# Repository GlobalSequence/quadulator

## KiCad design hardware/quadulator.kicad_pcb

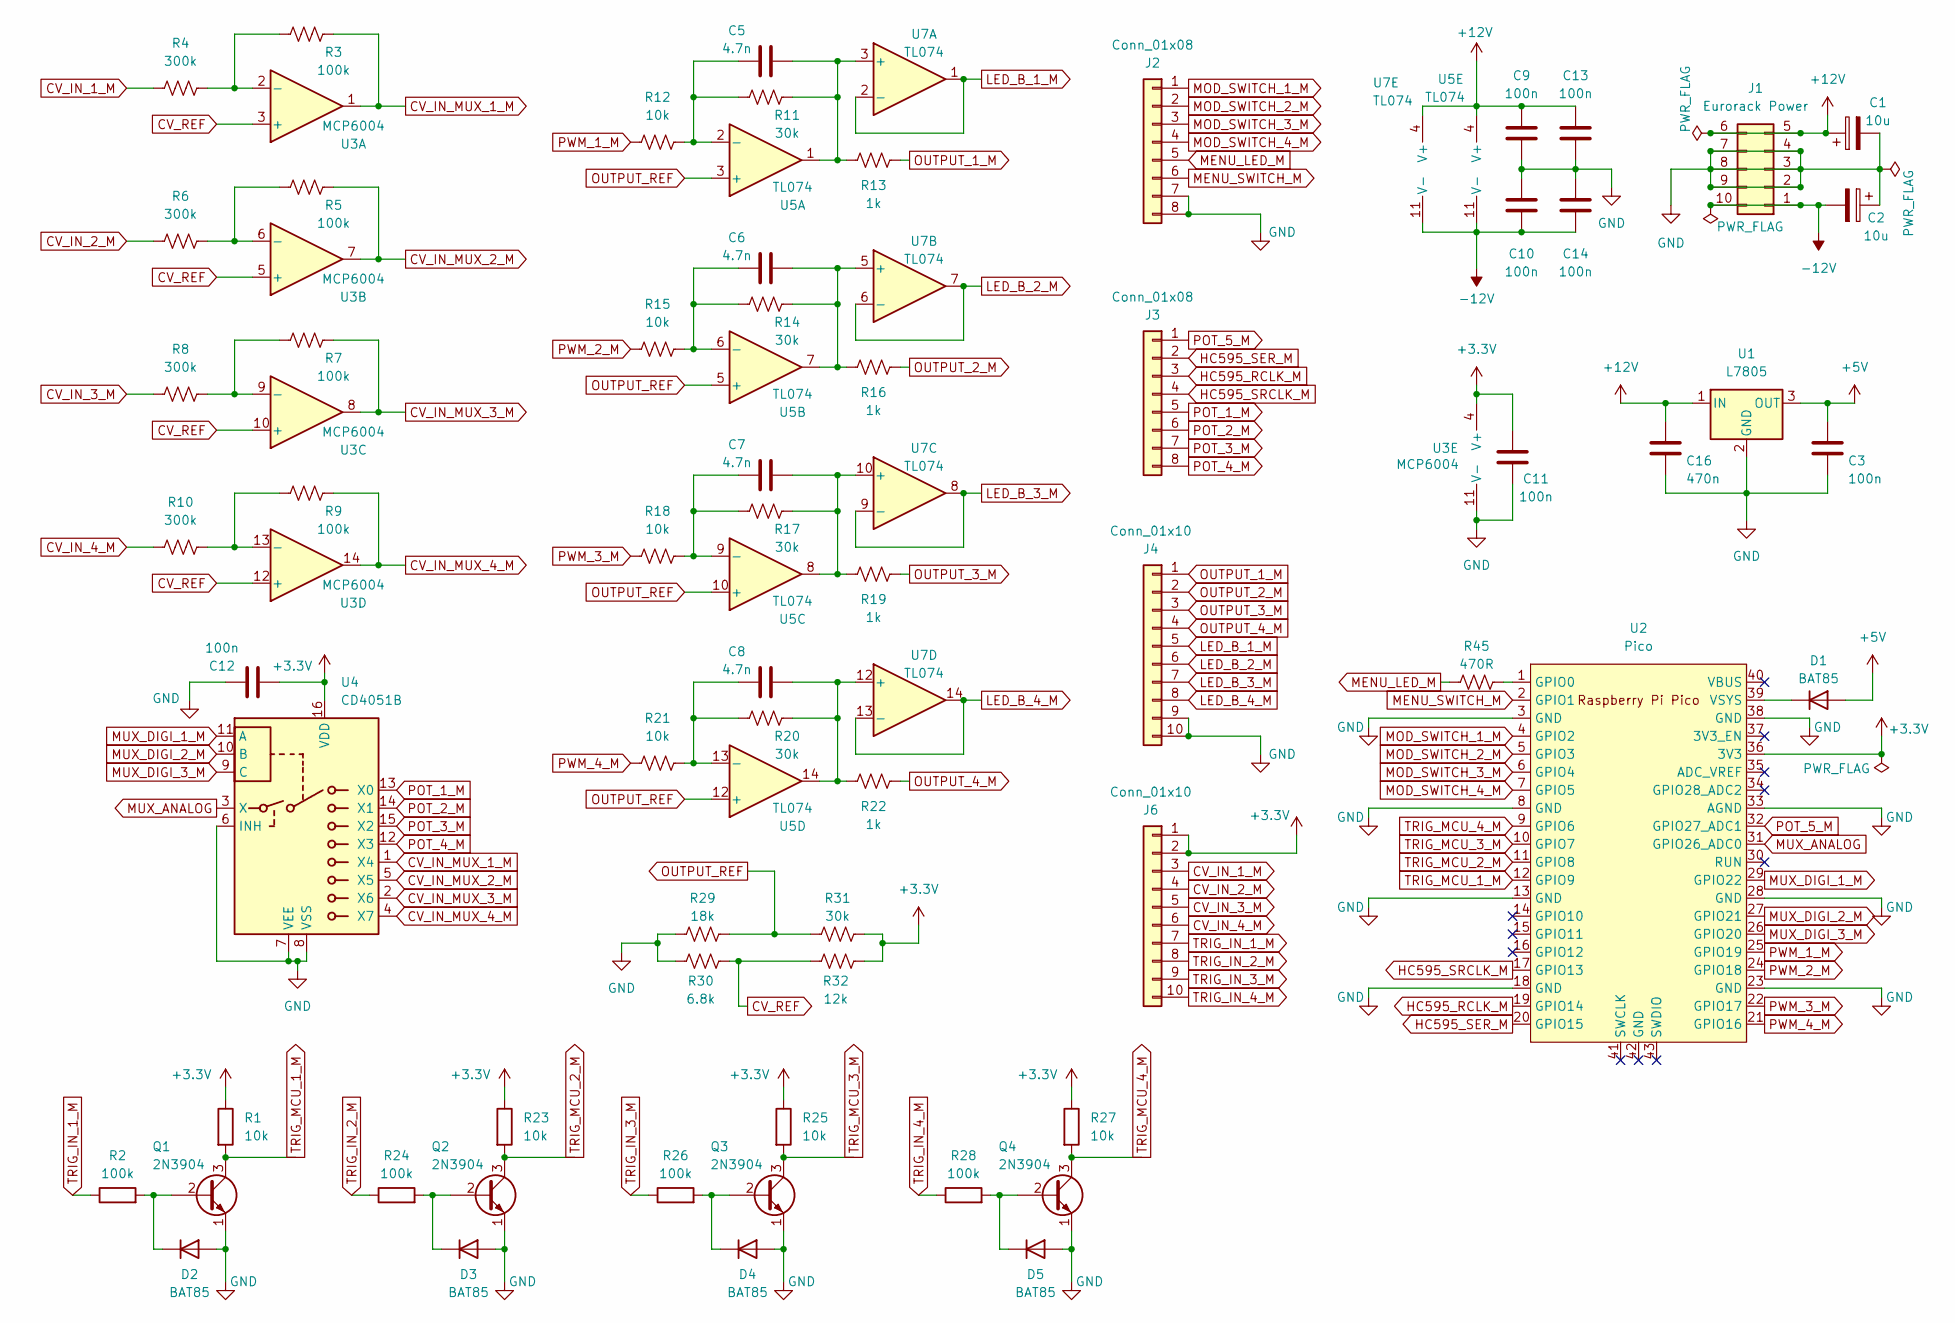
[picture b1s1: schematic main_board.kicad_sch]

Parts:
C1, C2: 10u; CP_Radial_D5.0mm_P2.50mm
C3, C9, C10, C11, C12, C13, C14: 100n; C_Disc_D5.0mm_W2.5mm_P5.00mm
C5, C6, C7, C8: 4.7n; C_Disc_D5.0mm_W2.5mm_P5.00mm
C16: 470n; C_Disc_D5.0mm_W2.5mm_P5.00mm
D1, D2, D3, D4, D5: BAT85; D_A-405_P7.62mm_Horizontal
J1: Eurorack Power; IDC-Header_2x05_P2.54mm_Vertical
J2, J3: Conn_01x08; PinSocket_1x08_P2.54mm_Vertical
J4, J6: Conn_01x10; PinSocket_1x10_P2.54mm_Vertical
Q1, Q2, Q3, Q4: 2N3904; TO-92L_Inline_Wide
R1, R12, R15, R18, R21, R23, R25, R27: 10k; R_Axial_DIN0207_L6.3mm_D2.5mm_P7.62mm_Horizontal
R2, R3, R5, R7, R9, R24, R26, R28: 100k; R_Axial_DIN0207_L6.3mm_D2.5mm_P7.62mm_Horizontal
R4, R6, R8, R10: 300k; R_Axial_DIN0207_L6.3mm_D2.5mm_P7.62mm_Horizontal
R11, R14, R17, R20, R31: 30k; R_Axial_DIN0207_L6.3mm_D2.5mm_P7.62mm_Horizontal
R13, R16, R19, R22: 1k; R_Axial_DIN0207_L6.3mm_D2.5mm_P7.62mm_Horizontal
R29: 18k; R_Axial_DIN0207_L6.3mm_D2.5mm_P7.62mm_Horizontal
R30: 6.8k; R_Axial_DIN0207_L6.3mm_D2.5mm_P7.62mm_Horizontal
R32: 12k; R_Axial_DIN0207_L6.3mm_D2.5mm_P7.62mm_Horizontal
R45: 470R; R_Axial_DIN0207_L6.3mm_D2.5mm_P7.62mm_Horizontal
U1: L7805; TO-220-3_Vertical
U2: Pico; RPi_Pico_SMD_TH
U3: MCP6004; DIP-14_W7.62mm_Socket
U4: CD4051B; DIP-16_W7.62mm_Socket
U5, U7: TL074; DIP-14_W7.62mm_Socket

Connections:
+3.3V: C11.1, C12.2, J6.1, J6.2, R1.1, R23.1, R25.1, R27.1, R31.2, R32.1, U2.36 (3V3), U3.4 (V+), U4.16 (VDD); also elsewhere on the board
+5V: C3.1, D1.2 (A), U1.3 (OUT)
+12V: C1.1, C9.1, C13.1, C16.1, J1.5, J1.6, U1.1 (IN), U5.4 (V+), U7.4 (V+)
-12V: C2.2, C10.2, C14.2, J1.1, J1.10, U5.11 (V-), U7.11 (V-)
CV_IN_1_M: J6.3, R4.1
CV_IN_2_M: J6.4, R6.1
CV_IN_3_M: J6.5, R8.1
CV_IN_4_M: J6.6, R10.1
CV_IN_MUX_1_M: R3.2, U3.1, U4.1 (X4)
CV_IN_MUX_2_M: R5.2, U3.7, U4.5 (X5)
CV_IN_MUX_3_M: R7.2, U3.8, U4.2 (X6)
CV_IN_MUX_4_M: R9.2, U3.14, U4.4 (X7)
CV_REF: R30.1, R32.2, U3.3 (+), U3.5 (+), U3.10 (+), U3.12 (+)
GND: C1.2, C2.1, C3.2, C9.2, C10.1, C11.2, C12.1, C13.2, C14.1, C16.2, D2.2 (A), D3.2 (A), D4.2 (A), D5.2 (A), J1.2, J1.3, J1.4, J1.7, J1.8, J1.9, J2.7, J2.8, J4.9, J4.10, Q1.1 (E), Q2.1 (E), Q3.1 (E), Q4.1 (E), R29.1, R30.2, U1.2 (GND), U2.3 (GND), U2.8 (GND), U2.13 (GND), U2.18 (GND), U2.23 (GND), U2.28 (GND), U2.33 (AGND), U2.38 (GND), U3.11 (V-), U4.6 (INH), U4.7 (VEE), U4.8 (VSS); also elsewhere on the board
HC595_RCLK_M: J3.3, U2.19 (GPIO14)
HC595_SER_M: J3.2, U2.20 (GPIO15)
HC595_SRCLK_M: J3.4, U2.17 (GPIO13)
LED_B_1_M: J4.5, U7.1, U7.2 (-)
LED_B_2_M: J4.6, U7.6 (-), U7.7
LED_B_3_M: J4.7, U7.8, U7.9 (-)
LED_B_4_M: J4.8, U7.13 (-), U7.14
MENU_LED_M: J2.5, R45.1
MENU_SWITCH_M: J2.6, U2.2 (GPIO1)
MOD_SWITCH_1_M: J2.1, U2.4 (GPIO2)
MOD_SWITCH_2_M: J2.2, U2.5 (GPIO3)
MOD_SWITCH_3_M: J2.3, U2.6 (GPIO4)
MOD_SWITCH_4_M: J2.4, U2.7 (GPIO5)
MUX_ANALOG: U2.31 (GPIO26_ADC0), U4.3 (X)
MUX_DIGI_1_M: U2.29 (GPIO22), U4.11 (A)
MUX_DIGI_2_M: U2.27 (GPIO21), U4.10 (B)
MUX_DIGI_3_M: U2.26 (GPIO20), U4.9 (C)
unnamed: D1.1 (K), U2.39 (VSYS)
unnamed: D2.1 (K), Q1.2 (B), R2.2
unnamed: D3.1 (K), Q2.2 (B), R24.2
unnamed: D4.1 (K), Q3.2 (B), R26.2
unnamed: D5.1 (K), Q4.2 (B), R28.2
unnamed: R45.2, U2.1 (GPIO0)
unnamed: R3.1, R4.2, U3.2 (-)
unnamed: R5.1, R6.2, U3.6 (-)
unnamed: R7.1, R8.2, U3.9 (-)
unnamed: R9.1, R10.2, U3.13 (-)
unnamed: C5.1, R11.1, R12.2, U5.2 (-)
unnamed: C6.1, R14.1, R15.2, U5.6 (-)
unnamed: C7.1, R17.1, R18.2, U5.9 (-)
unnamed: C8.1, R20.1, R21.2, U5.13 (-)
unnamed: C5.2, R11.2, R13.1, U5.1, U7.3 (+)
unnamed: C6.2, R14.2, R16.1, U5.7, U7.5 (+)
unnamed: C7.2, R17.2, R19.1, U5.8, U7.10 (+)
unnamed: C8.2, R20.2, R22.1, U5.14, U7.12 (+)
OUTPUT_1_M: J4.1, R13.2
OUTPUT_2_M: J4.2, R16.2
OUTPUT_3_M: J4.3, R19.2
OUTPUT_4_M: J4.4, R22.2
OUTPUT_REF: R29.2, R31.1, U5.3 (+), U5.5 (+), U5.10 (+), U5.12 (+)
POT_1_M: J3.5, U4.13 (X0)
POT_2_M: J3.6, U4.14 (X1)
POT_3_M: J3.7, U4.15 (X2)
POT_4_M: J3.8, U4.12 (X3)
POT_5_M: J3.1, U2.32 (GPIO27_ADC1)
PWM_1_M: R12.1, U2.25 (GPIO19)
PWM_2_M: R15.1, U2.24 (GPIO18)
PWM_3_M: R18.1, U2.22 (GPIO17)
PWM_4_M: R21.1, U2.21 (GPIO16)
TRIG_IN_1_M: J6.7, R2.1
TRIG_IN_2_M: J6.8, R24.1
TRIG_IN_3_M: J6.9, R26.1
TRIG_IN_4_M: J6.10, R28.1
TRIG_MCU_1_M: Q1.3 (C), R1.2, U2.12 (GPIO9)
TRIG_MCU_2_M: Q2.3 (C), R23.2, U2.11 (GPIO8)
TRIG_MCU_3_M: Q3.3 (C), R25.2, U2.10 (GPIO7)
TRIG_MCU_4_M: Q4.3 (C), R27.2, U2.9 (GPIO6)

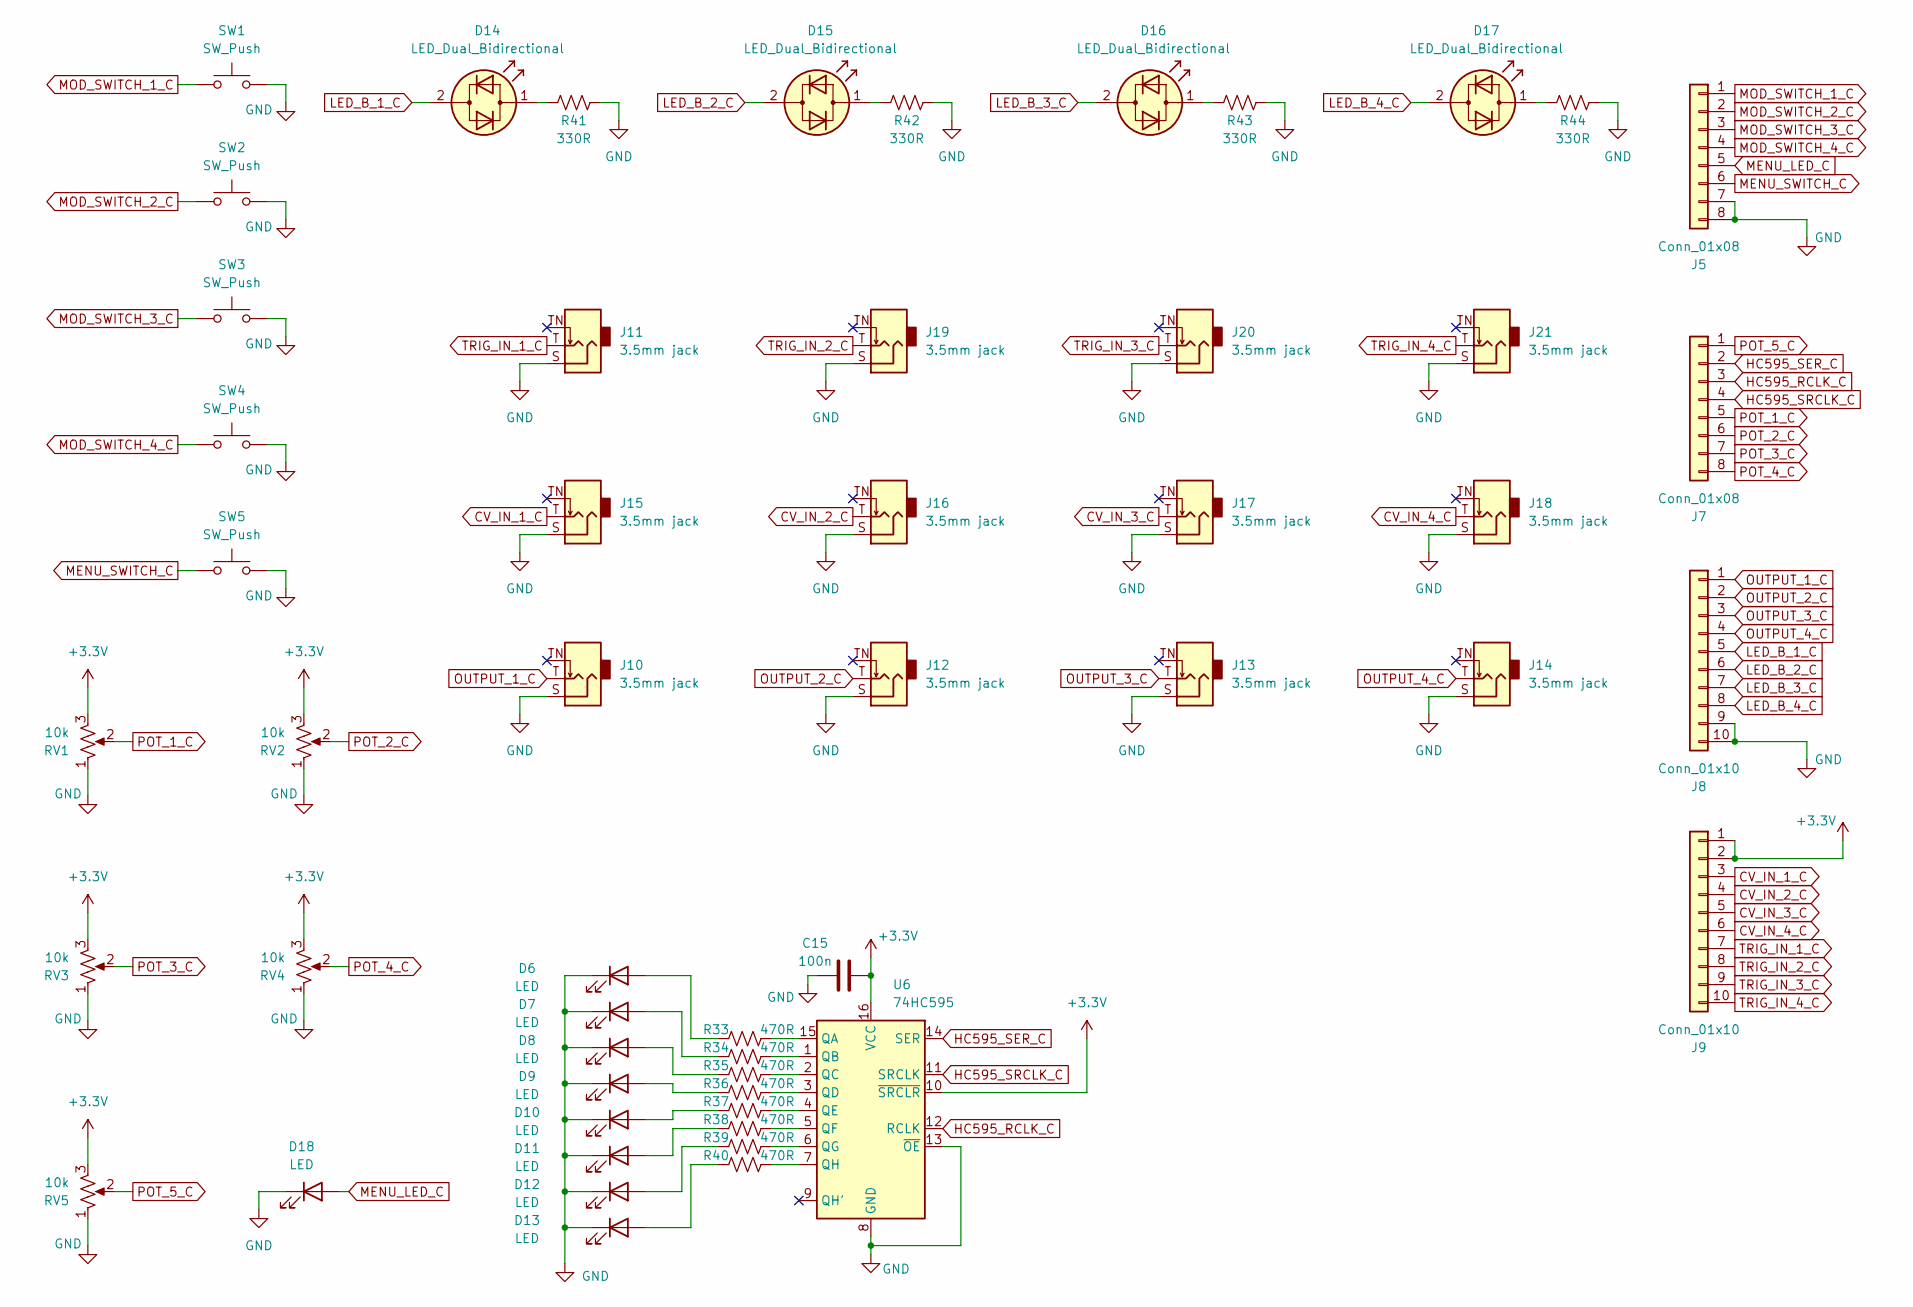
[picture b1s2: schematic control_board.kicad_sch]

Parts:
C15: 100n; C_Disc_D5.0mm_W2.5mm_P5.00mm
D6, D7, D8, D9, D10, D11, D12, D13, D18: LED; LED_D3.0mm
D14, D15, D16, D17: LED_Dual_Bidirectional; LED_D5.0mm
J5, J7: Conn_01x08; PinSocket_1x08_P2.54mm_Vertical
J8, J9: Conn_01x10; PinSocket_1x10_P2.54mm_Vertical
J10, J11, J12, J13, J14, J15, J16, J17, J18, J19, J20, J21: 3.5mm jack; Jack_3.5mm_QingPu_WQP-PJ398SM_Vertical_CircularHoles
R33, R34, R35, R36, R37, R38, R39, R40: 470R; R_Axial_DIN0207_L6.3mm_D2.5mm_P7.62mm_Horizontal
R41, R42, R43, R44: 330R; R_Axial_DIN0207_L6.3mm_D2.5mm_P7.62mm_Horizontal
RV1, RV2, RV3, RV4, RV5: 10k; Potentiometer_Alps_RK09K_Single_Vertical
SW1, SW2, SW3, SW4, SW5: SW_Push; SW_PUSH_6mm
U6: 74HC595; DIP-16_W7.62mm_Socket

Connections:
+3.3V: C15.2, J9.1, J9.2, RV1.3, RV2.3, RV3.3, RV4.3, RV5.3, U6.10 (~SRCLR), U6.16 (VCC); also elsewhere on the board
CV_IN_1_C: J9.3, J15.T
CV_IN_2_C: J9.4, J16.T
CV_IN_3_C: J9.5, J17.T
CV_IN_4_C: J9.6, J18.T
GND: C15.1, D6.1 (K), D7.1 (K), D8.1 (K), D9.1 (K), D10.1 (K), D11.1 (K), D12.1 (K), D13.1 (K), D18.1 (K), J5.7, J5.8, J8.9, J8.10, J10.S, J11.S, J12.S, J13.S, J14.S, J15.S, J16.S, J17.S, J18.S, J19.S, J20.S, J21.S, R41.2, R42.2, R43.2, R44.2, RV1.1, RV2.1, RV3.1, RV4.1, RV5.1, SW1.2, SW2.2, SW3.2, SW4.2, SW5.2, U6.8 (GND), U6.13 (~OE); also elsewhere on the board
HC595_RCLK_C: J7.3, U6.12 (RCLK)
HC595_SER_C: J7.2, U6.14 (SER)
HC595_SRCLK_C: J7.4, U6.11 (SRCLK)
LED_B_1_C: D14.2 (AK), J8.5
LED_B_2_C: D15.2 (AK), J8.6
LED_B_3_C: D16.2 (AK), J8.7
LED_B_4_C: D17.2 (AK), J8.8
MENU_LED_C: D18.2 (A), J5.5
MENU_SWITCH_C: J5.6, SW5.1
MOD_SWITCH_1_C: J5.1, SW1.1
MOD_SWITCH_2_C: J5.2, SW2.1
MOD_SWITCH_3_C: J5.3, SW3.1
MOD_SWITCH_4_C: J5.4, SW4.1
unnamed: D6.2 (A), R33.1
unnamed: D7.2 (A), R34.1
unnamed: D8.2 (A), R35.1
unnamed: D9.2 (A), R36.1
unnamed: D10.2 (A), R37.1
unnamed: D11.2 (A), R38.1
unnamed: D12.2 (A), R39.1
unnamed: D13.2 (A), R40.1
unnamed: D14.1 (KA), R41.1
unnamed: D15.1 (KA), R42.1
unnamed: D16.1 (KA), R43.1
unnamed: D17.1 (KA), R44.1
unnamed: R33.2, U6.15 (QA)
unnamed: R34.2, U6.1 (QB)
unnamed: R35.2, U6.2 (QC)
unnamed: R36.2, U6.3 (QD)
unnamed: R37.2, U6.4 (QE)
unnamed: R38.2, U6.5 (QF)
unnamed: R39.2, U6.6 (QG)
unnamed: R40.2, U6.7 (QH)
OUTPUT_1_C: J8.1, J10.T
OUTPUT_2_C: J8.2, J12.T
OUTPUT_3_C: J8.3, J13.T
OUTPUT_4_C: J8.4, J14.T
POT_1_C: J7.5, RV1.2
POT_2_C: J7.6, RV2.2
POT_3_C: J7.7, RV3.2
POT_4_C: J7.8, RV4.2
POT_5_C: J7.1, RV5.2
TRIG_IN_1_C: J9.7, J11.T
TRIG_IN_2_C: J9.8, J19.T
TRIG_IN_3_C: J9.9, J20.T
TRIG_IN_4_C: J9.10, J21.T

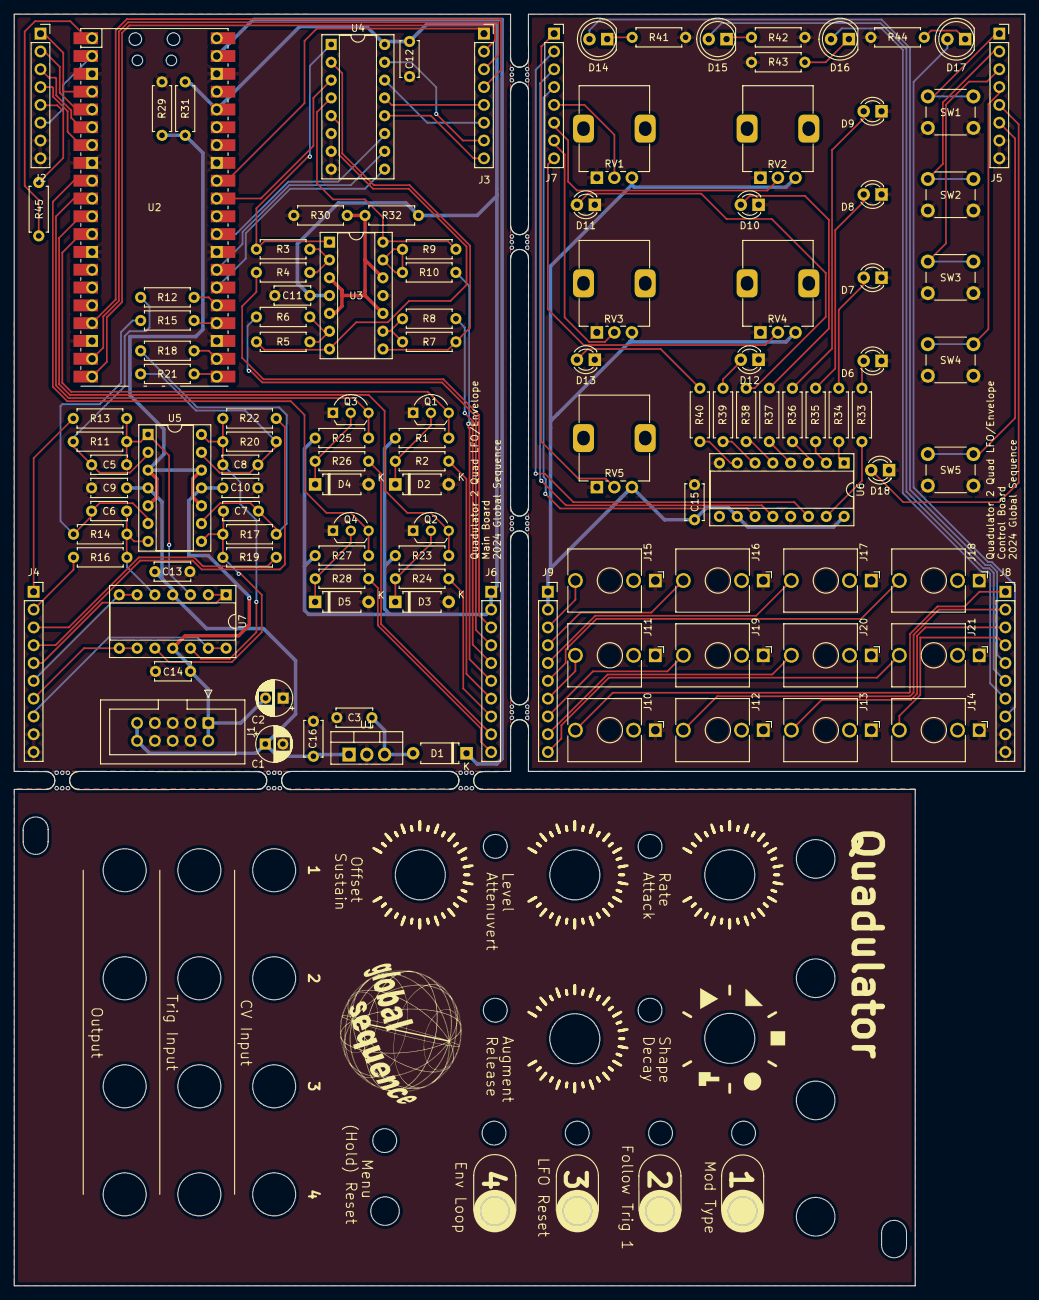
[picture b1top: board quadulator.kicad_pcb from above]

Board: 2 copper layers, 144.1 x 181.3 mm, 127 parts (0 on the bottom side), 121 nets.

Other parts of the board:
mouse-bite-2.54mm-slot, mouse-bite-2.54mm-slot#2, mouse-bite-2.54mm-slot#3, mouse-bite-2.54mm-slot#4, mouse-bite-2.54mm-slot#5, mouse-bite-2.54mm-slot#6, mouse-bite-2.54mm-slot#7: VAL**; mouse-bite-2.54mm-slot

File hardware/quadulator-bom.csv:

"Reference","Value","Footprint","Qty"
"C1,C2","10u","Capacitor_THT:CP_Radial_D5.0mm_P2.50mm","2"
"C3,C9,C10,C11,C12,C13,C14,C15","100n","Capacitor_THT:C_Disc_D5.0mm_W2.5mm_P5.00mm","8"
"C5,C6,C7,C8","4.7n","Capacitor_THT:C_Disc_D5.0mm_W2.5mm_P5.00mm","4"
"C16","470n","Capacitor_THT:C_Disc_D5.0mm_W2.5mm_P5.00mm","1"
"D1,D2,D3,D4,D5","BAT85","Diode_THT:D_A-405_P7.62mm_Horizontal","5"
"D6,D7,D8,D9,D10,D11,D12,D13,D18","LED","LED_THT:LED_D3.0mm","9"
"D14,D15,D16,D17","LED_Dual_Bidirectional","LED_THT:LED_D5.0mm","4"
"J1","Eurorack Power","Connector_IDC:IDC-Header_2x05_P2.54mm_Vertical","1"
"J2,J3,J5,J7","Conn_01x08","Connector_PinSocket_2.54mm:PinSocket_1x08_P2.54mm_Vertical","4"
"J4,J6,J8,J9","Conn_01x10","Connector_PinSocket_2.54mm:PinSocket_1x10_P2.54mm_Vertical","4"
"J10,J11,J12,J13,J14,J15,J16,J17,J18,J19,J20,J21","3.5mm jack","Connector_Audio:Jack_3.5mm_QingPu_WQP-PJ398SM_Vertical_CircularHoles","12"
"Q1,Q2,Q3,Q4","2N3904","Package_TO_SOT_THT:TO-92L_Inline_Wide","4"
"R1,R12,R15,R18,R21,R23,R25,R27","10k","Resistor_THT:R_Axial_DIN0207_L6.3mm_D2.5mm_P7.62mm_Horizontal","8"
"R2,R3,R5,R7,R9,R24,R26,R28","100k","Resistor_THT:R_Axial_DIN0207_L6.3mm_D2.5mm_P7.62mm_Horizontal","8"
"R4,R6,R8,R10","300k","Resistor_THT:R_Axial_DIN0207_L6.3mm_D2.5mm_P7.62mm_Horizontal","4"
"R11,R14,R17,R20,R31","30k","Resistor_THT:R_Axial_DIN0207_L6.3mm_D2.5mm_P7.62mm_Horizontal","5"
"R13,R16,R19,R22","1k","Resistor_THT:R_Axial_DIN0207_L6.3mm_D2.5mm_P7.62mm_Horizontal","4"
"R29","18k","Resistor_THT:R_Axial_DIN0207_L6.3mm_D2.5mm_P7.62mm_Horizontal","1"
"R30","6.8k","Resistor_THT:R_Axial_DIN0207_L6.3mm_D2.5mm_P7.62mm_Horizontal","1"
"R32","12k","Resistor_THT:R_Axial_DIN0207_L6.3mm_D2.5mm_P7.62mm_Horizontal","1"
"R33,R34,R35,R36,R37,R38,R39,R40,R45","470R","Resistor_THT:R_Axial_DIN0207_L6.3mm_D2.5mm_P7.62mm_Horizontal","9"
"R41,R42,R43,R44","330R","Resistor_THT:R_Axial_DIN0207_L6.3mm_D2.5mm_P7.62mm_Horizontal","4"
"RV1,RV2,RV3,RV4,RV5","10k","Potentiometer_THT:Potentiometer_Alps_RK09K_Single_Vertical","5"
"SW1,SW2,SW3,SW4,SW5","SW_Push","Button_Switch_THT:SW_PUSH_6mm","5"
"U1","L7805","Package_TO_SOT_THT:TO-220-3_Vertical","1"
"U2","Pico","MCU_RaspberryPi_and_Boards:RPi_Pico_SMD_TH","1"
"U3","MCP6004","Package_DIP:DIP-14_W7.62mm_Socket","1"
"U4","CD4051B","Package_DIP:DIP-16_W7.62mm_Socket","1"
"U5,U7","TL074","Package_DIP:DIP-14_W7.62mm_Socket","2"
"U6","74HC595","Package_DIP:DIP-16_W7.62mm_Socket","1"

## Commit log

2025-01-09 created repository
2025-01-12 added bom
2025-01-12 updated bom
2025-02-17 updated quadulator.pdf to schematic.pdf
